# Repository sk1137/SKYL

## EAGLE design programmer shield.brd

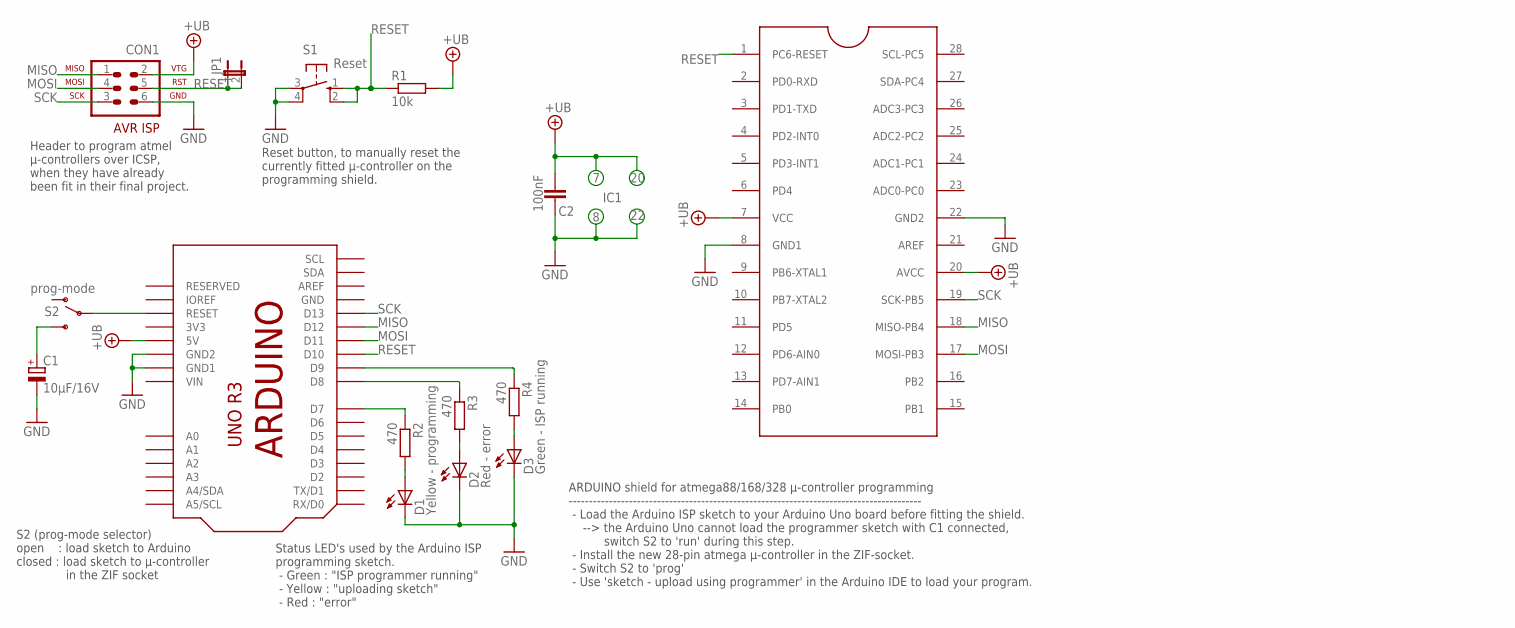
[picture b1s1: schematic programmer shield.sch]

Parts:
C1: 10µF/16V; E2,5-6E
C2: 100nF; C050-025X075
CON1: ICSP; AVR-ISP-6
D1: Yellow - programming; LED3MM
D2: Red - error; LED3MM
D3: Green - ISP running; LED3MM
IC1: Atmega88/168/328; DIL28-3-ZIF_NARROW
JP1: JP1E; JP1
R1: 10k; 0207/7
R2, R3, R4: 470; 0204/5
S1: Reset; B3F-10XX
S2: prog-mode; MINI_SPDT_SWITCH-9.0X4.0MM
U$1: Arduino Uno; ARDUINO-R3

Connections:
3V3: U$1.3V (3V3)
+UB: C2.2, CON1.2, IC1.7 (VCC), IC1.20 (AVCC), R1.2, U$1.5V
GND: C1.-, C2.1, CON1.6, D1.K (C), D2.K (C), D3.K (C), IC1.8 (GND1), IC1.22 (GND2), S1.3, S1.4 (P1), U$1.GND, U$1.GND1, U$1.GND2
MISO: CON1.1, IC1.18 (MISO-PB4), U$1.D12
MOSI: CON1.4, IC1.17 (MOSI-PB3), U$1.D11
unnamed: C1.+, S2.3 (S)
unnamed: R4.1, U$1.D9
unnamed: R2.1, U$1.D7
unnamed: R3.1, U$1.D8
unnamed: D1.A, R2.2
unnamed: D2.A, R3.2
unnamed: D3.A, R4.2
unnamed: S2.2, U$1.RESET
RESET: CON1.5, IC1.1 (PC6-RESET), JP1.1, JP1.2, R1.1, S1.1 (S), S1.2 (S1), U$1.D10
SCK: CON1.3, IC1.19 (SCK-PB5), U$1.D13
VIN: U$1.VIN

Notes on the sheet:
IC1
Header to program atmel µ-controllers over ICSP, when they have already been fit in their final project.
Reset button, to manually reset the currently fitted µ-controller on the programming shield.
Status LED's used by the Arduino ISP programming sketch. - Green : "ISP programmer running" - Yellow : "uploading sketch" - Red : "error"
ARDUINO shield for atmega88/168/328 µ-controller programming ---------------------------------------------------------------------------------------- - Load the Arduino ISP sketch to your Arduino Uno board before fitting the shield. --> the Arduino Uno cannot load the programmer sketch with C1 conn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
S2 (prog-mode selector) open : load sketch to Arduino closed : load sketch to µ-controller in the ZIF socket

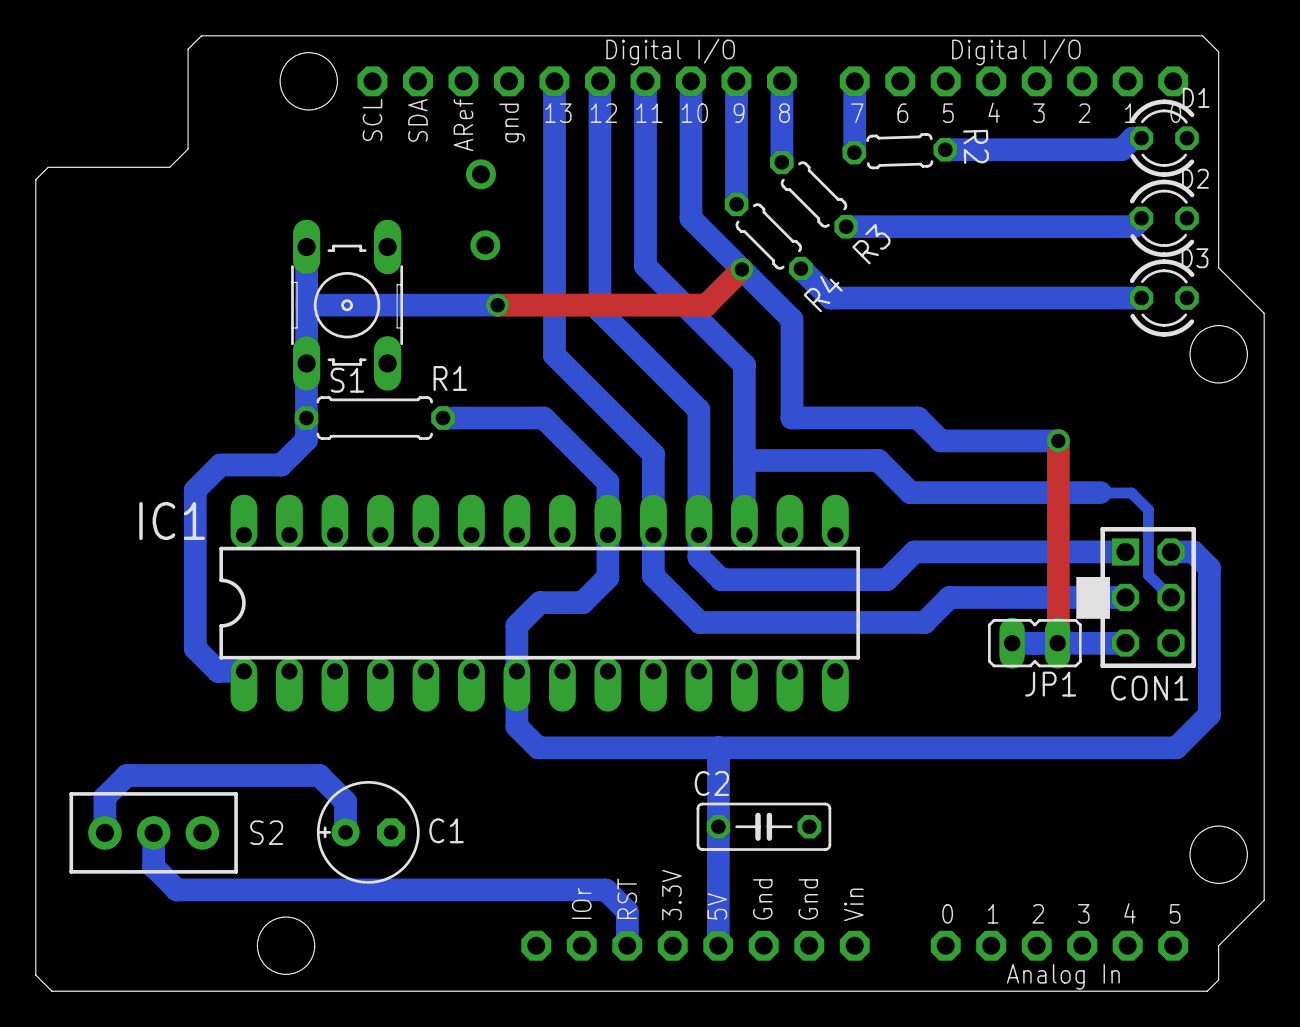
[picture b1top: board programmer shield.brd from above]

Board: 2 copper layers, 68.6 x 53.3 mm, 21 parts (1 on the bottom side), 14 nets.

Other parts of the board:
U$2: COPYRIGHT-LOGO-3-B
U$3, U$7: 3X-LOGO-10-B
U$4: COPYRIGHT-LOGO-3-T
U$5: 3X-LOGO-5-B
U$6: 3X-LOGO-5-T
